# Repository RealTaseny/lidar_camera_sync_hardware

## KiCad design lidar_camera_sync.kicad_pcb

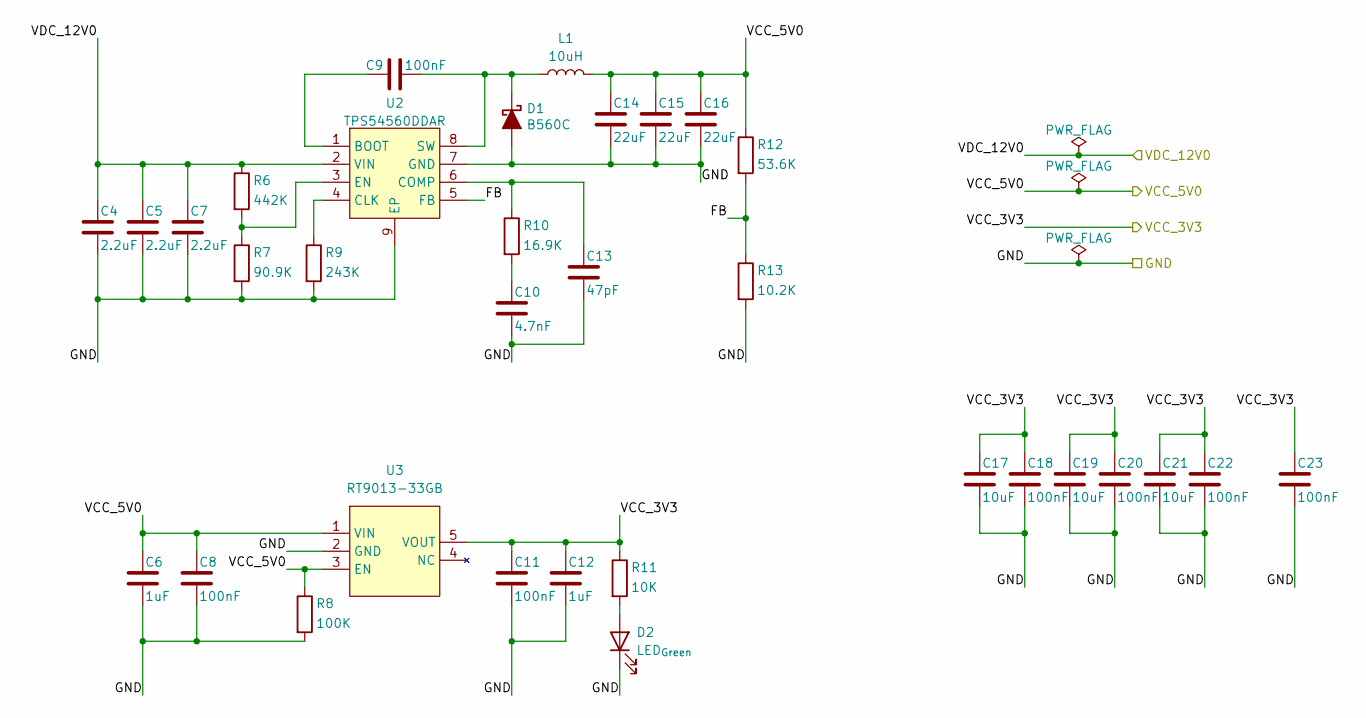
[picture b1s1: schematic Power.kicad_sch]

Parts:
C4, C5, C7: 2.2uF; C_0805_2012Metric
C6, C12: 1uF; C_0603_1608Metric
C8, C9, C11, C18, C20, C22, C23: 100nF; C_0603_1608Metric
C10: 4.7nF; C_0603_1608Metric
C13: 47pF; C_0603_1608Metric
C14, C15, C16: 22uF; C_0805_2012Metric
C17, C19, C21: 10uF; C_0603_1608Metric
D1: B560C; D_SMC
D2: LED_{Green}; LED_0603_1608Metric
L1: 10uH; SPM7054VT-100M-D
R6: 442K; R_0603_1608Metric
R7: 90.9K; R_0603_1608Metric
R8: 100K; R_0603_1608Metric
R9: 243K; R_0603_1608Metric
R10: 16.9K; R_0603_1608Metric
R11: 10K; R_0603_1608Metric
R12: 53.6K; R_0603_1608Metric
R13: 10.2K; R_0603_1608Metric
U2: TPS54560DDAR; SOIC8-4.9x5.4_P1.27
U3: RT9013-33GB; SOT-23-5

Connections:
/MCU/GND: C4.2, C5.2, C6.2, C7.2, C8.2, C10.2, C11.2, C12.2, C13.2, C14.2, C15.2, C16.2, C17.2, C18.2, C19.2, C20.2, C21.2, C22.2, C23.2, D1.2 (A), D2.1 (K), R7.2, R8.2, R9.2, R13.2, U2.7 (GND), U2.9 (EP), U3.2 (GND); also elsewhere on the board
/MCU/VCC_3V3: C11.1, C12.1, C17.1, C18.1, C19.1, C20.1, C21.1, C22.1, C23.1, R11.1, U3.5 (VOUT); also elsewhere on the board
/Peripheral/12V_CAMERA: C4.1, C5.1, C7.1, R6.1, U2.2 (VIN); also elsewhere on the board
/Peripheral/VCC_5V0: C6.1, C8.1, C14.1, C15.1, C16.1, L1.2, R8.1, R12.1, U3.1 (VIN), U3.3 (EN); also elsewhere on the board
/Power/FB: R12.2, R13.1, U2.5 (FB)
unnamed: C10.1, R10.2
unnamed: C9.2, D1.1 (K), L1.1, U2.8 (SW)
unnamed: D2.2 (A), R11.2
unnamed: C9.1, U2.1 (BOOT)
unnamed: R9.1, U2.4 (CLK)
unnamed: C13.1, R10.1, U2.6 (COMP)
unnamed: R6.2, R7.1, U2.3 (EN)

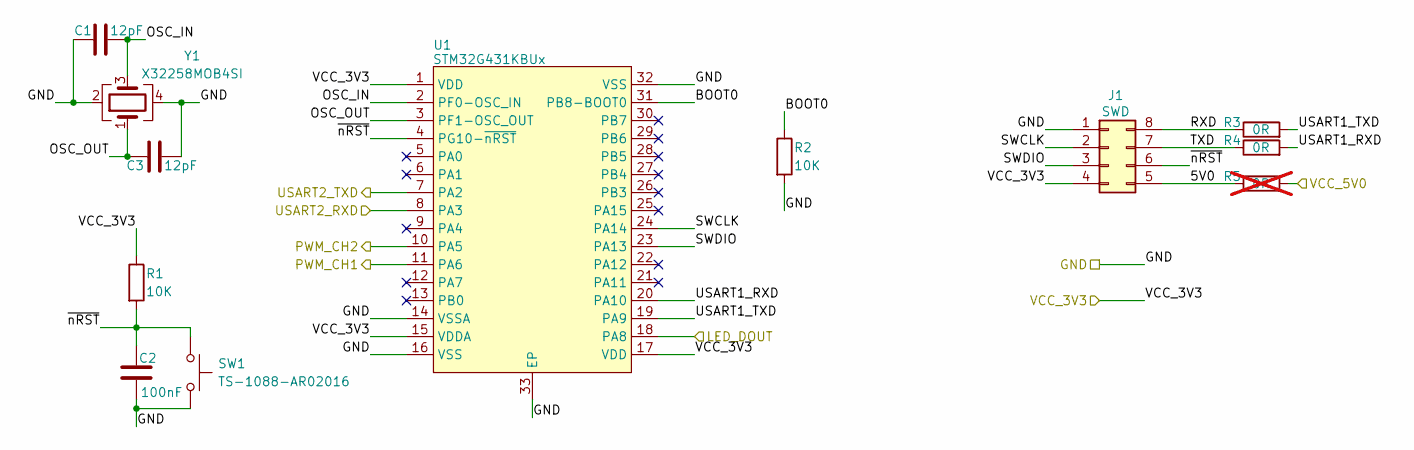
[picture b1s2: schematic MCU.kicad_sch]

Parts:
C1, C3: 12pF; C_0603_1608Metric
C2: 100nF; C_0603_1608Metric
J1: SWD; Pinheader_2x04_P2.54mm
R1, R2: 10K; R_0603_1608Metric
R3, R4: 0R; R_0603_1608Metric
R5: 0R; R_0603_1608Metric; not fitted
SW1: TS-1088-AR02016
U1: STM32G431KBUx; UFQFPN32-5.3x5.3_P0.5
Y1: X32258MOB4SI; SMD3225

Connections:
/MCU/5V0: J1.5, R5.1; also elsewhere on the board
/MCU/BOOT0: R2.1, U1.31 (PB8-BOOT0)
/MCU/GND: C1.2, C2.2, C3.1, J1.1, R2.2, SW1.2, U1.14 (VSSA), U1.16 (VSS), U1.32 (VSS), U1.33 (EP), Y1.2, Y1.4; also elsewhere on the board
/MCU/LED_DOUT: U1.18 (PA8); also elsewhere on the board
/MCU/OSC_IN: C1.1, U1.2 (PF0-OSC_IN), Y1.3
/MCU/OSC_OUT: C3.2, U1.3 (PF1-OSC_OUT), Y1.1
/MCU/PWM_CH1: U1.11 (PA6); also elsewhere on the board
/MCU/PWM_CH2: U1.10 (PA5); also elsewhere on the board
/MCU/RXD: J1.8, R3.1; also elsewhere on the board
/MCU/SWCLK: J1.2, U1.24 (PA14); also elsewhere on the board
/MCU/SWDIO: J1.3, U1.23 (PA13); also elsewhere on the board
/MCU/TXD: J1.7, R4.1; also elsewhere on the board
/MCU/USART1_RXD: R4.2, U1.20 (PA10)
/MCU/USART1_TXD: R3.2, U1.19 (PA9)
/MCU/USART2_RXD: U1.8 (PA3); also elsewhere on the board
/MCU/USART2_TXD: U1.7 (PA2); also elsewhere on the board
/MCU/VCC_3V3: J1.4, R1.1, U1.1 (VDD), U1.15 (VDDA), U1.17 (VDD); also elsewhere on the board
/MCU/~nRST: C2.1, J1.6, R1.2, SW1.1, U1.4 (PG10-~nRST); also elsewhere on the board
/Peripheral/VCC_5V0: R5.2; also elsewhere on the board

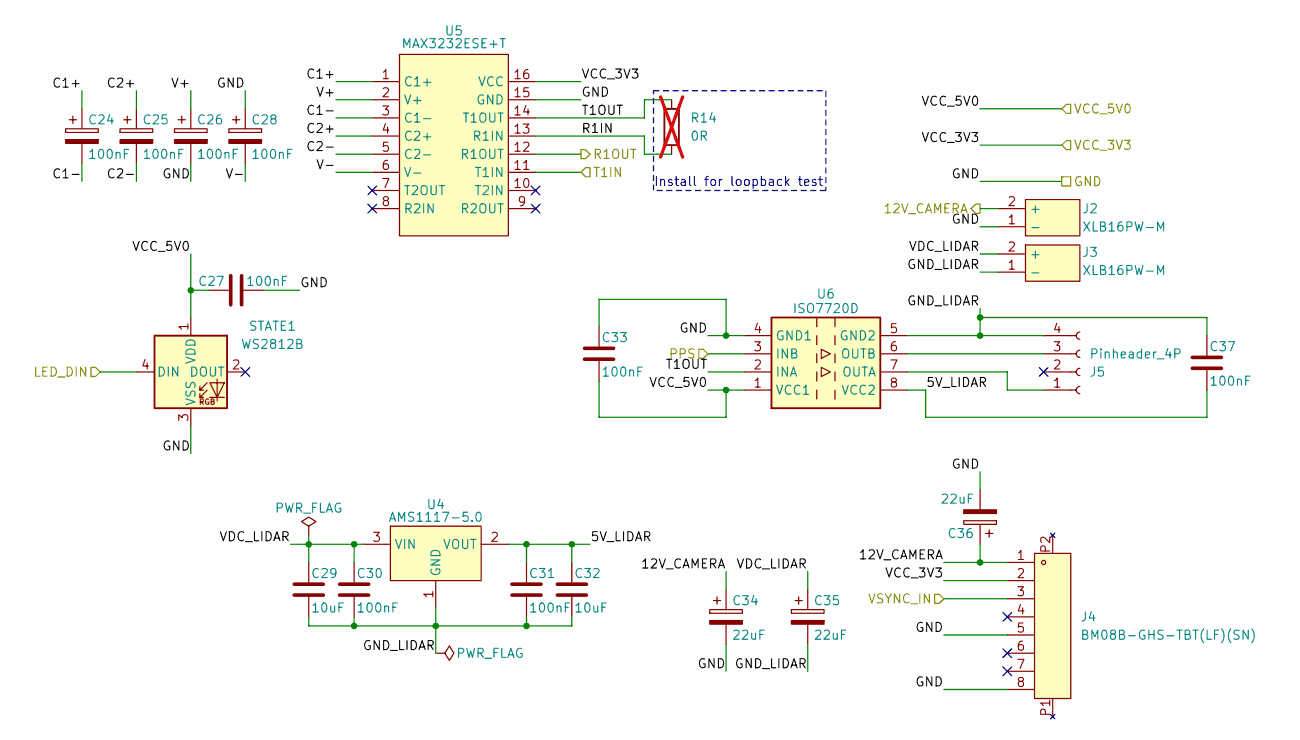
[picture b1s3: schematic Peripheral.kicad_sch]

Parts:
C24, C25, C26, C28: 100nF; CP_Elec_4x5.4
C27, C30, C31, C33, C37: 100nF; C_0603_1608Metric
C29, C32: 10uF; C_0603_1608Metric
C34, C35, C36: 22uF; CP_Elec_6.3x5.4
J2, J3: XLB16PW-M
J4: BM08B-GHS-TBT(LF)(SN); BM08B-GHS-TBT(LF)(SN)(N)
J5: Pinheader_4P; PinHeader_1x04_P2.54mm_Vertical
R14: 0R; R_0603_1608Metric; not fitted
STATE1: WS2812B; LED_WS2812B_PLCC4_5.0x5.0mm_P3.2mm
U4: AMS1117-5.0; SOT223
U5: MAX3232ESE+T; SOIC16-4.95x8.9_P1.27
U6: ISO7720D; SOIC8-4.9x5.4_P1.27_NO_EP

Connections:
/MCU/GND: C26.2, C27.2, C28.1, C33.1, C34.2, C36.2, J2.1 (-), J4.5, J4.8, STATE1.3 (VSS), U5.15 (GND), U6.4 (GND1); also elsewhere on the board
/MCU/PWM_CH1: U6.3 (INB); also elsewhere on the board
/MCU/PWM_CH2: J4.3; also elsewhere on the board
/MCU/USART2_RXD: U5.12 (R1OUT); also elsewhere on the board
/MCU/USART2_TXD: U5.11 (T1IN); also elsewhere on the board
/MCU/VCC_3V3: J4.2, U5.16 (VCC); also elsewhere on the board
/Peripheral/5V_LIDAR: C31.1, C32.1, C37.2, U4.2 (VOUT), U4.4 (VOUT), U6.8 (VCC2)
/Peripheral/12V_CAMERA: C34.1, C36.1, J4.1; also elsewhere on the board
/Peripheral/C1+: C24.1, U5.1 (C1+)
/Peripheral/C1-: C24.2, U5.3 (C1-)
/Peripheral/C2+: C25.1, U5.4 (C2+)
/Peripheral/C2-: C25.2, U5.5 (C2-)
/Peripheral/GND_LIDAR: C29.2, C30.2, C31.2, C32.2, C35.2, C37.1, J3.1 (-), J5.4, U4.1 (GND), U6.5 (GND2); also elsewhere on the board
/Peripheral/R1IN: R14.2, U5.13 (R1IN)
/Peripheral/T1OUT: R14.1, U5.14 (T1OUT), U6.2 (INA)
/Peripheral/V+: C26.1, U5.2 (V+)
/Peripheral/V-: C28.2, U5.6 (V-)
/Peripheral/VCC_5V0: C27.1, C33.2, STATE1.1 (VDD), U6.1 (VCC1); also elsewhere on the board
/Peripheral/VDC_LIDAR: C29.1, C30.1, C35.1, J3.2 (+), U4.3 (VIN); also elsewhere on the board
unnamed 35: J5.1, U6.7 (OUTA); also elsewhere on the board
unnamed 36: J5.3, U6.6 (OUTB); also elsewhere on the board

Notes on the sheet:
Install for loopback test

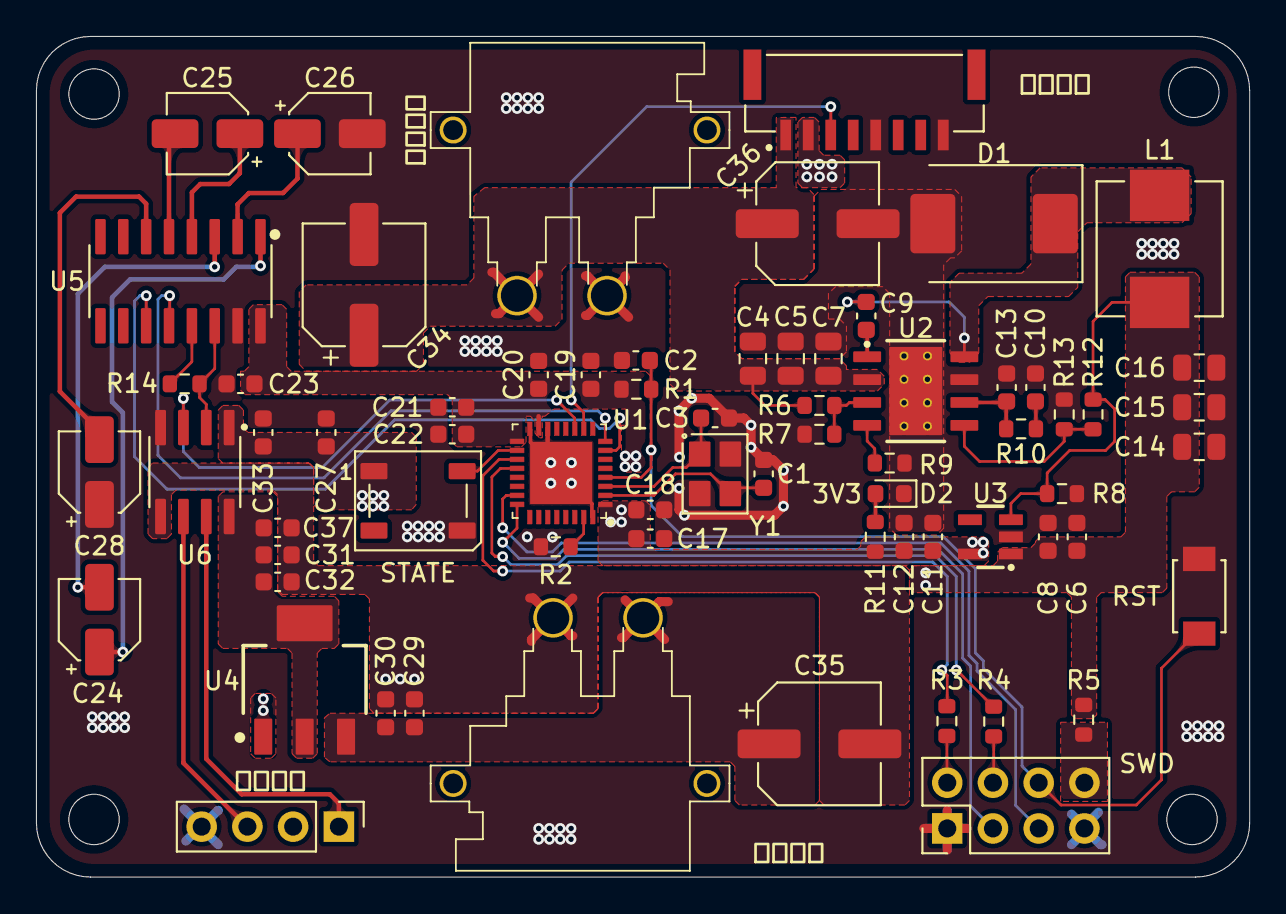
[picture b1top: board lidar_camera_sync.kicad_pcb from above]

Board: 2 copper layers, 67.4 x 46.7 mm, 68 parts (0 on the bottom side), 41 nets.

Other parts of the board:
RST: TS-1088-AR02016
STATE: WS2812B; LED_WS2812B_PLCC4_5.0x5.0mm_P3.2mm
SWD: SWD; Pinheader_2x04_P2.54mm
相机电源: XLB16PW-M
雷达接口: Pinheader_4P; PinHeader_1x04_P2.54mm_Vertical
雷达电源: XLB16PW-M

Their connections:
/MCU/5V0: SWD.5; also elsewhere on the board
/MCU/GND: RST.2, STATE.3 (VSS), SWD.1, 相机电源.1 (-); also elsewhere on the board
/MCU/LED_DOUT: STATE.4 (DIN); also elsewhere on the board
/MCU/RXD: SWD.8; also elsewhere on the board
/MCU/SWCLK: SWD.2; also elsewhere on the board
/MCU/SWDIO: SWD.3; also elsewhere on the board
/MCU/TXD: SWD.7; also elsewhere on the board
/MCU/VCC_3V3: SWD.4; also elsewhere on the board
/MCU/~nRST: RST.1, SWD.6; also elsewhere on the board
/Peripheral/12V_CAMERA: 相机电源.2 (+); also elsewhere on the board
/Peripheral/GND_LIDAR: 雷达接口.4, 雷达电源.1 (-); also elsewhere on the board
/Peripheral/VCC_5V0: STATE.1 (VDD); also elsewhere on the board
/Peripheral/VDC_LIDAR: 雷达电源.2 (+); also elsewhere on the board
unnamed 35: 雷达接口.1; also elsewhere on the board
unnamed 36: 雷达接口.3; also elsewhere on the board

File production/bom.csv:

Designator,Footprint,Quantity,Value,LCSC Part #
"C1, C3",0603,2,12pF,
C10,0603,1,4.7nF,
"C11, C18, C2, C20, C22, C23, C27, C30, C31, C33, C37, C8, C9",0603,13,100nF,
"C12, C6",0603,2,1uF,
C13,0603,1,47pF,
"C14, C15, C16",0805,3,22uF,
"C17, C19, C21, C29, C32",0603,5,10uF,
"C24, C25, C26, C28",CP_Elec_4x5.4,4,100nF,
"C34, C35, C36",CP_Elec_6.3x5.4,3,22uF,
"C4, C5, C7",0805,3,2.2uF,
D1,D_SMC,1,B560C,
D2,0603,1,LED_{Green},
J4,BM08B-GHS-TBT(LF)(SN)(N),1,BM08B-GHS-TBT(LF)(SN),
L1,SPM7054VT-100M-D,1,10uH,
"R1, R11, R2",0603,3,10K,
R10,0603,1,16.9K,
R12,0603,1,53.6K,
R13,0603,1,10.2K,
"R14, R3, R4, R5",0603,4,0R,
R6,0603,1,442K,
R7,0603,1,90.9K,
R8,0603,1,100K,
R9,0603,1,243K,
RST,TS-1088-AR02016,1,TS-1088-AR02016,
STATE,LED_WS2812B_PLCC4_5.0x5.0mm_P3.2mm,1,WS2812B,
SWD,Pinheader_2x04_P2.54mm,1,SWD,
U1,UFQFPN32-5.3x5.3_P0.5,1,STM32G431KBUx,
U2,SOIC8-4.9x5.4_P1.27,1,TPS54560DDAR,
U3,SOT-23-5,1,RT9013-33GB,
U4,SOT223,1,AMS1117-5.0,
U5,SOIC16-4.95x8.9_P1.27,1,MAX3232ESE+T,
U6,SOIC8-4.9x5.4_P1.27_NO_EP,1,ISO7720D,
Y1,SMD3225,1,X32258MOB4SI,
"相机电源, 雷达电源",XLB16PW-M,2,XLB16PW-M,
雷达接口,PinHeader_1x04_P2.54mm_Vertical,1,Pinheader_4P,

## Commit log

2025-11-20 create new project
2025-11-22 [New]: 完成MCU部分电路原理图\JIRA-ID: N/A\完成MCU部分原理图绘制以及部分Power部分原理图绘制
2025-11-23 [New]: 完成整个原理图绘制和ERC检查
    JIRA-ID: N/A
    完成整个原理图绘制和ERC检查
2025-11-24 [Fix]: 添加雷达供电隔离
    JIRA-ID: N/A
    添加雷达信号隔离电路，检查原理图错误，新增原理图符号
2025-11-24 [New]: 添加封装
    JIRA-ID: N/A
    添加除电阻电容外的封装和3D模型
2025-11-24 [Fix]: 添加漏掉的提交
    JIRA-ID: N/A
    添加漏掉的提交
2025-11-24 [Modify]: 完成封装的分配和PCB更新
    JIRA-ID: N/A
    完成封装的分配和从原理图到PCB的初始更新;完成DRC检查
2025-11-25 [Modify]: 添加输入输出去耦电容以及WS2812B灯珠
    JIRA-ID: N/A
    添加输入输出去耦电容以及WS2812B灯珠
2025-11-25 [Modify]: 修复一些封装错误, 完成基本Layout器件摆放
    JIRA-ID: N/A
    修复一些封装错误, 完成基本Layout器件摆放
2025-11-25 [New]: 完成PCB编辑以及DRC设计检查
    JIRA-ID: N/A
    完成PCB编辑以及DRC设计检查, 等待打板验证以及导出BOM表
2025-11-25 [New]: 生成嘉立创打板文件和BOM表
    JIRA-ID: N/A
    生成嘉立创打板文件和BOM表
